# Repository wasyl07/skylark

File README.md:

# skylark
Drone control board based on AM335 BeagleBone Black and Ardupilot

## Repository layout

- `BeagleBone-cape/` - KiCad project of the Skylark cape
- `br2-skylark/` - Buildroot external tree: A/B (RAUC) Linux image with systemd, see [docs/buildroot.md](docs/buildroot.md)
- `buildroot-2025.02.15/` - Buildroot itself (plus the legacy single-slot config, [docs/buildroot-legacy.md](docs/buildroot-legacy.md))
- `scripts/` - image checks (`verify-image.sh`, `check-defconfig.sh`)
- `ardupilot/` - ArduPilot (submodule)
- `docker/` - PRU toolchain container and PRU firmware
- `docs/` - documentation
  - [buildroot.md](docs/buildroot.md) - building, A/B updates, services, flashing, serial console, CAN, RTC/NTP
  - [FUNCTIONS.md](docs/FUNCTIONS.md) - requirements
  - [bringup-2026-10-05.md](docs/bringup-2026-10-05.md) - first bring-up: test results, cape rev 1 issues, board state
  - [prus.md](docs/prus.md) - PRU usage: PRU1 servo/ESC PWM firmware design and ArduPilot interface

## Quick start

```sh
make setup && make                 # -> output/images/sdcard.img, update.raucb
sh scripts/verify-image.sh
```

## Quick reference

- Serial console: UART4, P9.11 (RX) / P9.13 (TX), 115200 8N1, 3.3 V
- Network: DHCP, `skylark.local` (mDNS), SSH as root
- Updates: `rauc install update.raucb` (A/B slots, automatic fallback after 3 failed boots)
- CAN: `can0` (DCAN1, P9.24/P9.26), 1 Mbit/s, up at boot
- RTC: DS1307 on I2C2 (`/dev/rtc1`), synced from NTP when online (cape rev 1: RTC does not keep time, see bring-up record)

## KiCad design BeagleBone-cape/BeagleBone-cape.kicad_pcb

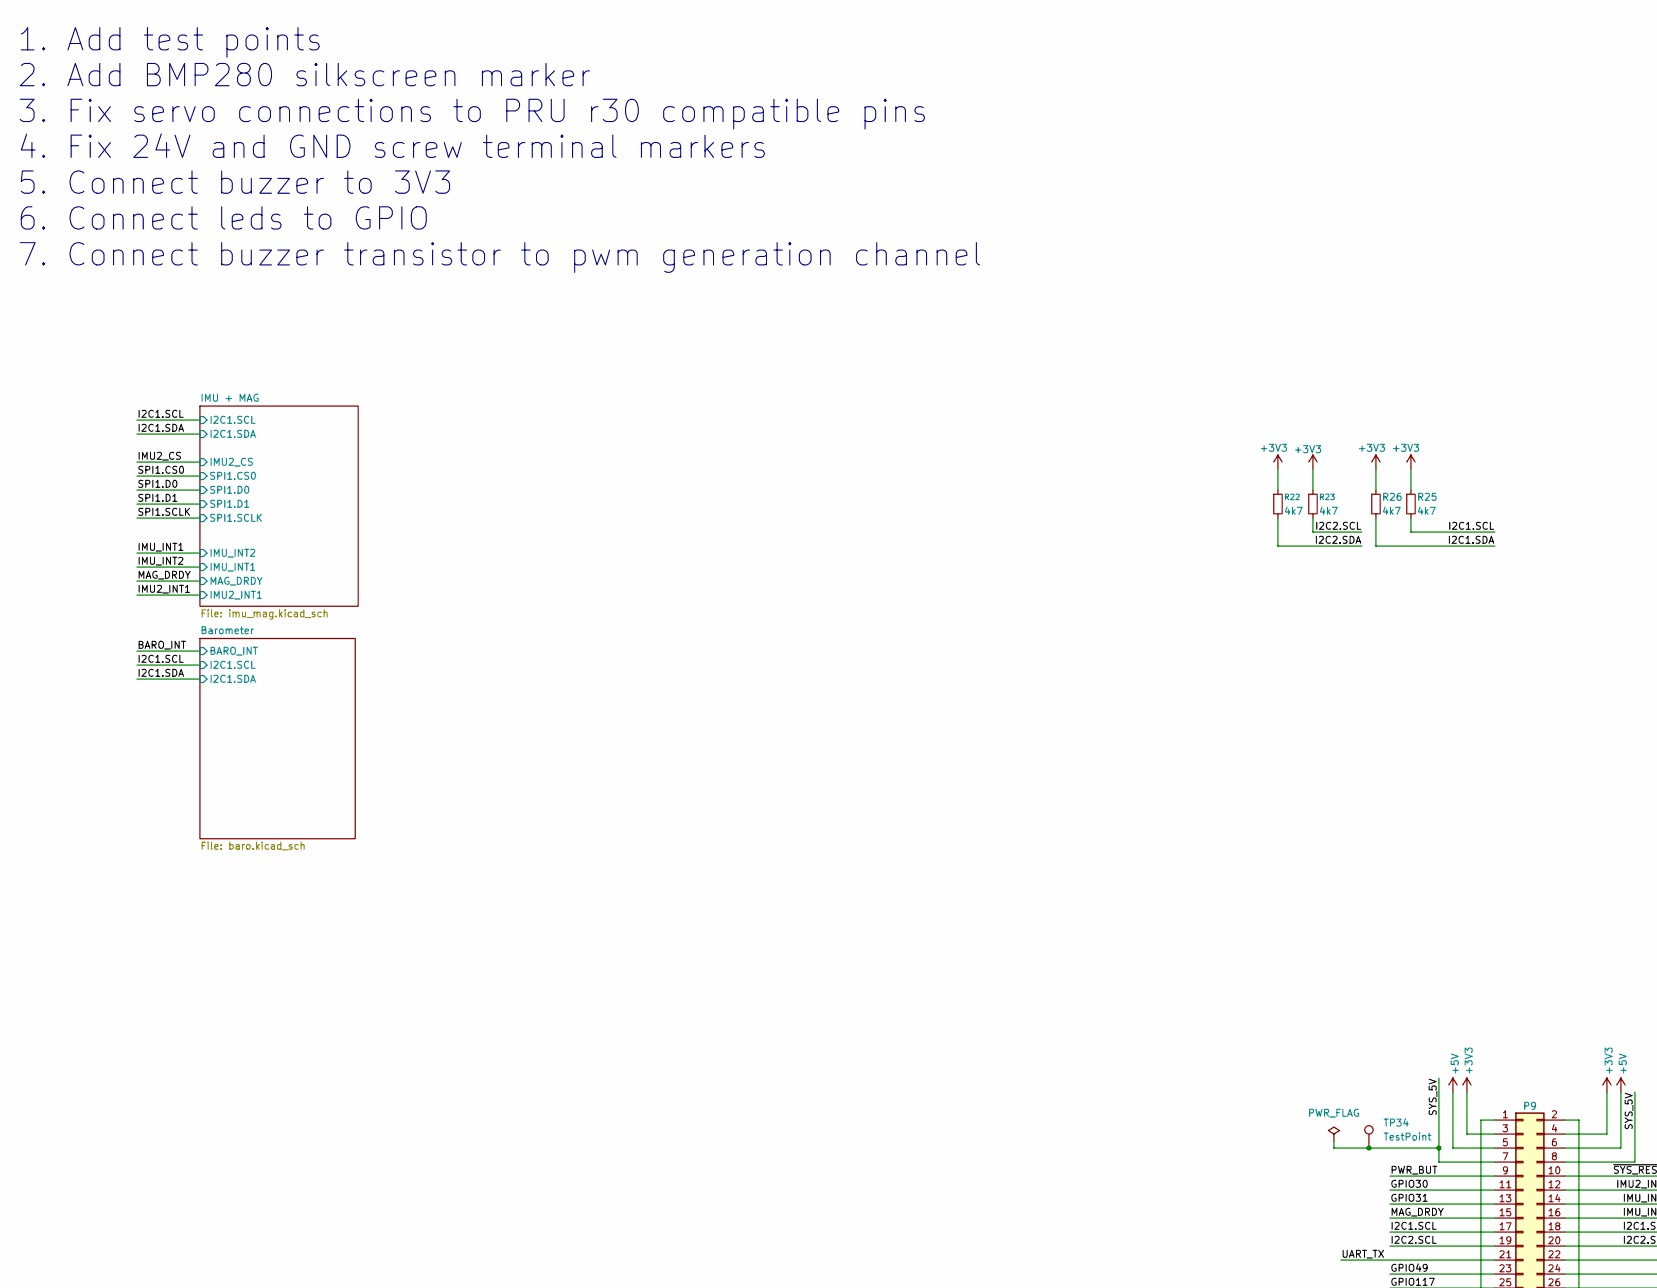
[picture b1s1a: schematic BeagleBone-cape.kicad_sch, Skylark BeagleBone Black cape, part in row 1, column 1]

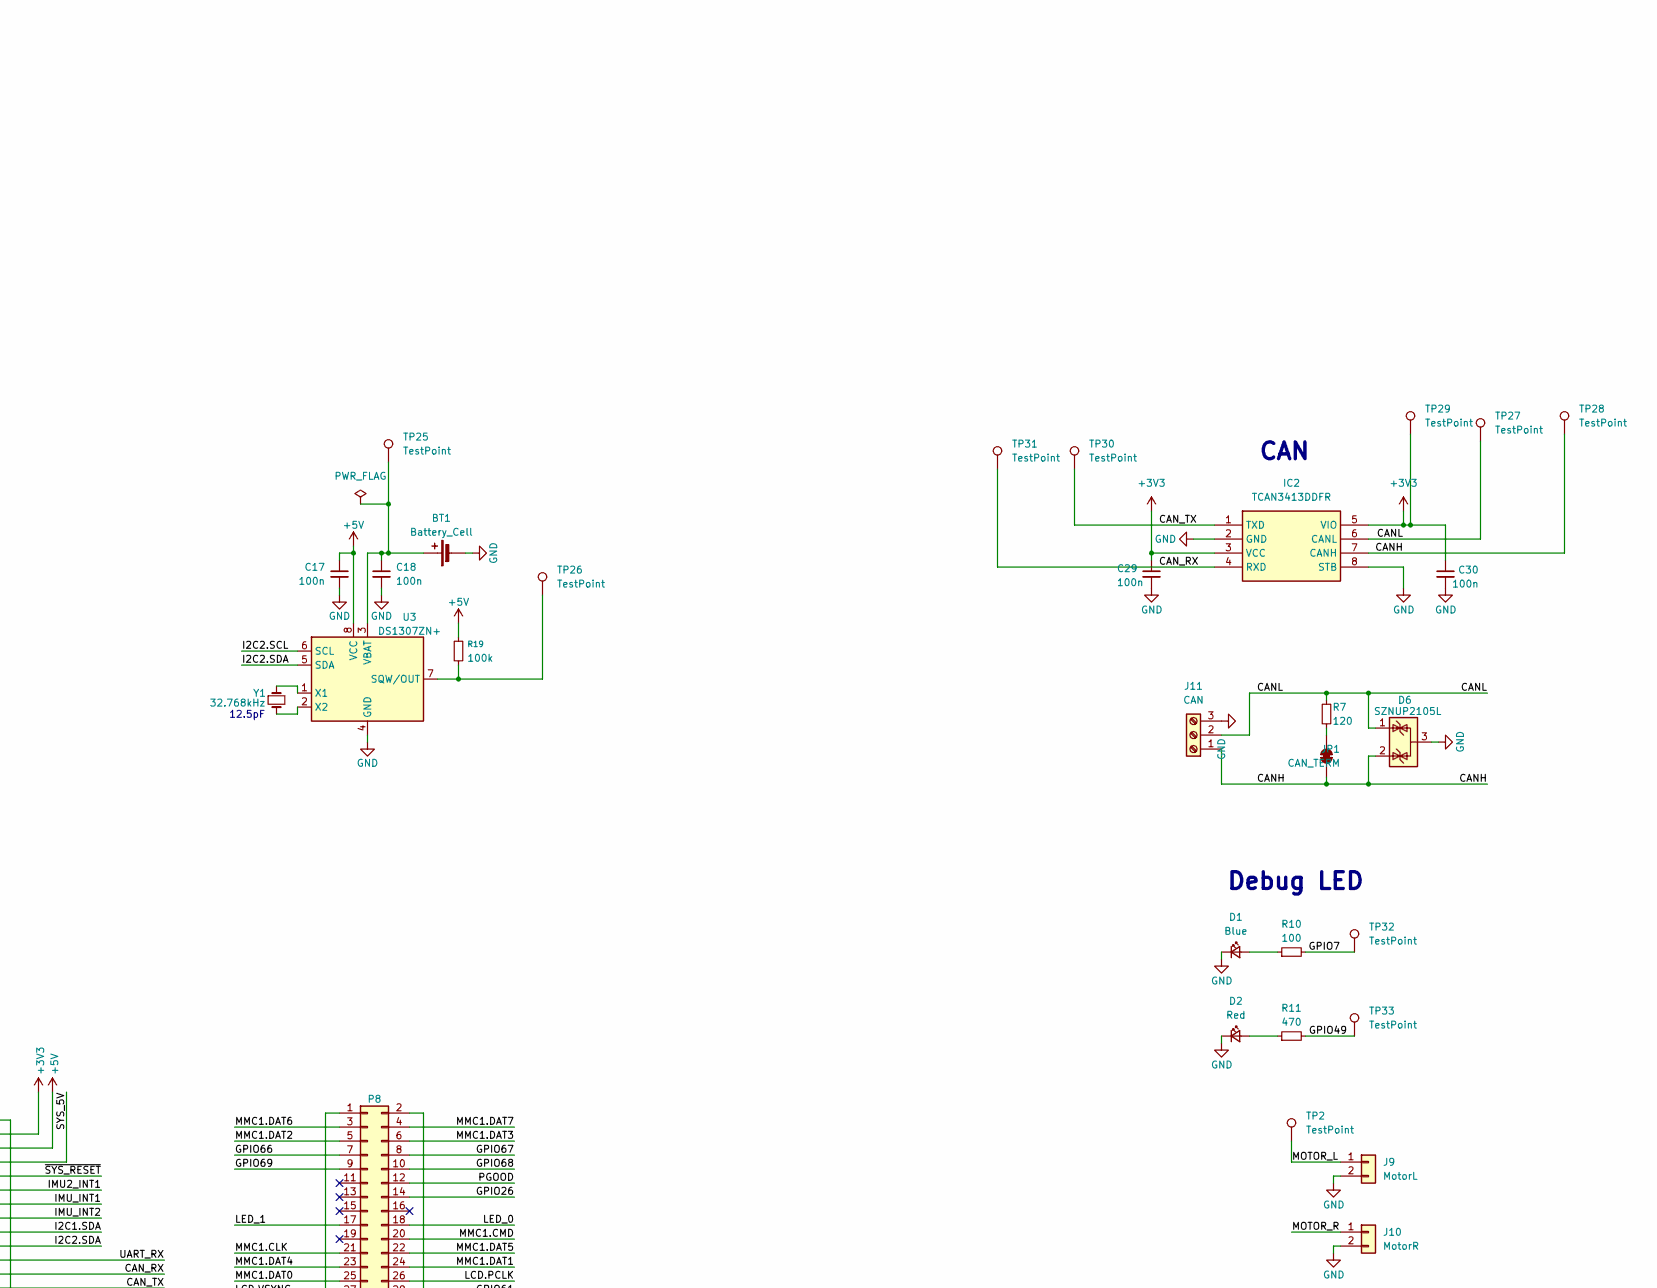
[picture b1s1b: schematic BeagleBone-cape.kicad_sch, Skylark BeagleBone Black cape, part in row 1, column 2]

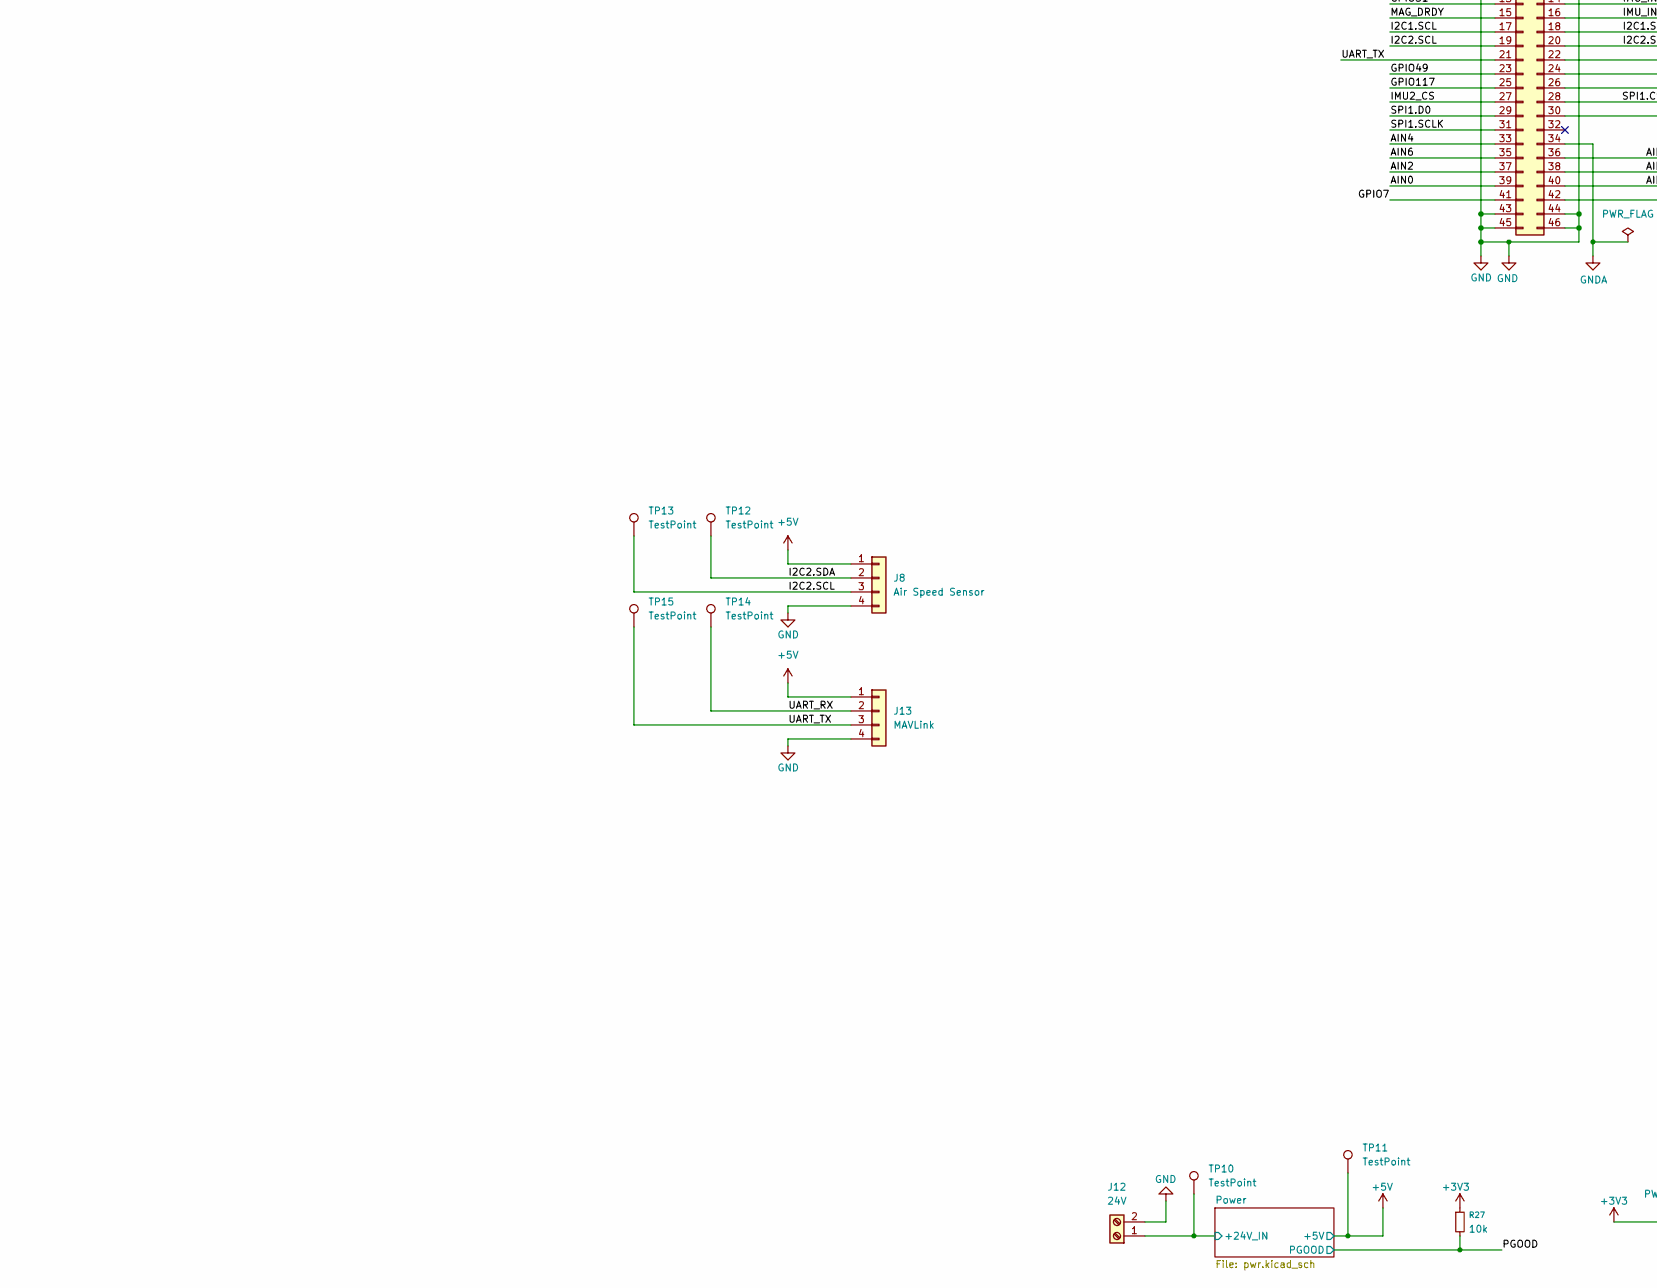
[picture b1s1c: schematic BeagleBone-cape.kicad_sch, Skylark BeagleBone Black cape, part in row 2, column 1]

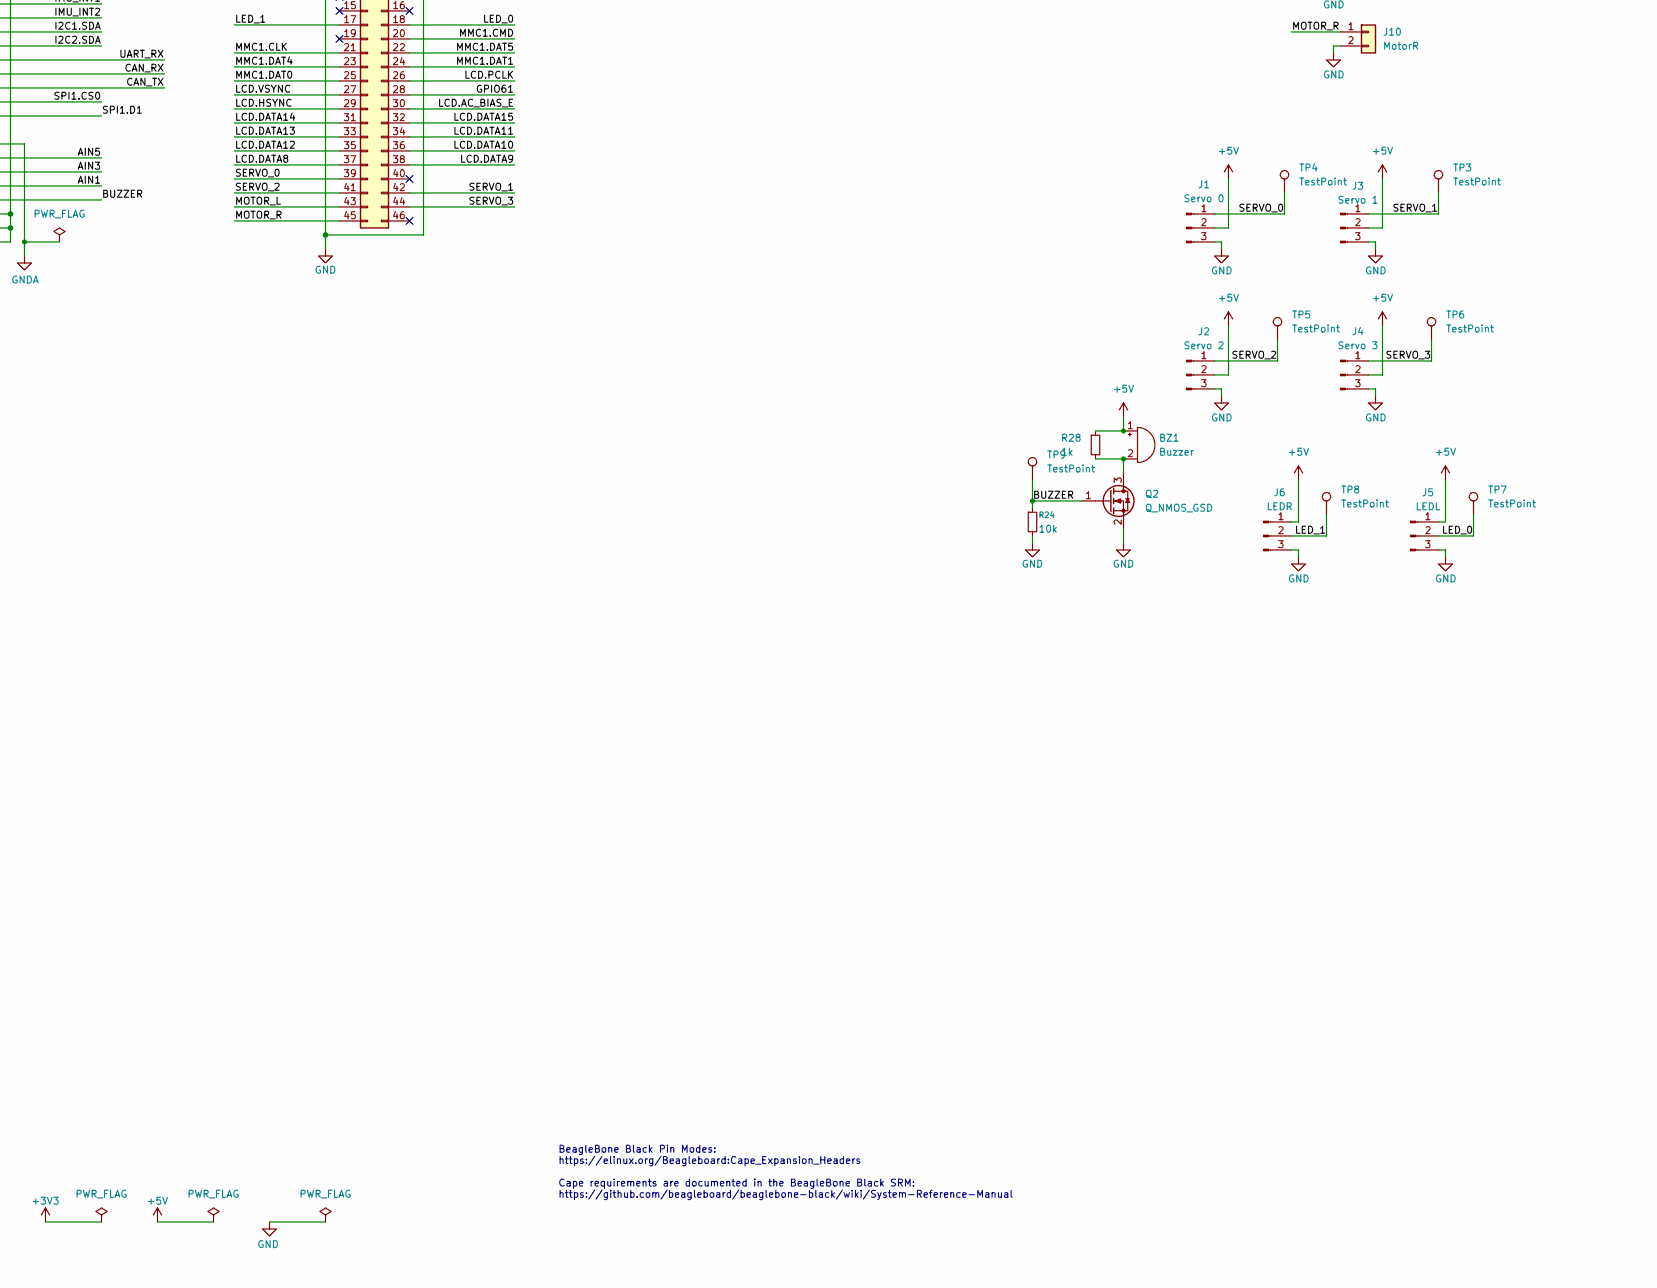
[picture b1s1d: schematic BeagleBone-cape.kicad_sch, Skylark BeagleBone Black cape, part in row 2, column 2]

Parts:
BT1: Battery_Cell; BatteryHolder_MYOUNG_BS-07-A1BJ001_CR2032; Manufacturer_Part_Number BS-07-A1BJ001; LCSC C2979167
BZ1: Buzzer; Buzzer_TDK_PS1240P02BT_D12.2mm_H6.5mm; Manufacturer_Part_Number PS1240P02BT; LCSC C76871
C17, C18, C29, C30: 100n; C_0603_1608Metric_Pad1.08x0.95mm_HandSolder; Manufacturer_Part_Number CC0603KRX7R9BB104; LCSC C14663
D1: Blue; D_0603_1608Metric
D2: Red; D_0603_1608Metric
D6: SZNUP2105L; SOT-23; Manufacturer_Part_Number SZNUP2105LT1G; LCSC C233494
IC2: TCAN3413DDFR; SOT65P280X110-8N; Manufacturer_Part_Number TCAN3413DDFR; Mouser Part Number 595-TCAN3413DDFR
J1: Servo 0; JST_EH_B3B-EH-A_1x03_P2.50mm_Vertical
J2: Servo 2; JST_EH_B3B-EH-A_1x03_P2.50mm_Vertical
J3: Servo 1; JST_EH_B3B-EH-A_1x03_P2.50mm_Vertical
J4: Servo 3; JST_EH_B3B-EH-A_1x03_P2.50mm_Vertical
J5: LEDL; JST_EH_B3B-EH-A_1x03_P2.50mm_Vertical
J6: LEDR; JST_EH_B3B-EH-A_1x03_P2.50mm_Vertical
J8: Air Speed Sensor; JST_EH_B4B-EH-A_1x04_P2.50mm_Vertical
J9: MotorL; JST_EH_B2B-EH-A_1x02_P2.50mm_Vertical
J10: MotorR; JST_EH_B2B-EH-A_1x02_P2.50mm_Vertical
J11: CAN; TerminalBlock_Xinya_XY308-2.54-3P_1x03_P2.54mm_Horizontal
J12: 24V; TerminalBlock_Xinya_XY308-2.54-2P_1x02_P2.54mm_Horizontal
J13: MAVLink; JST_EH_B4B-EH-A_1x04_P2.50mm_Vertical
JP1: CAN_TERM; SolderJumper-2_P1.3mm_Bridged_RoundedPad1.0x1.5mm
P8, P9: BeagleBone_Black_Header; PinHeader_2x23_P2.54mm_Vertical
Q2: Q_NMOS_GSD; SOT-23; Manufacturer_Part_Number BSS138LT1G; LCSC C82045
R7: 120; R_0603_1608Metric_Pad0.98x0.95mm_HandSolder; Manufacturer_Part_Number 0603WAF1200T5E; LCSC C22787
R10: 100; R_0603_1608Metric_Pad0.98x0.95mm_HandSolder; Manufacturer_Part_Number RC0603FR-07100RL; LCSC C105588
R11: 470; R_0603_1608Metric_Pad0.98x0.95mm_HandSolder; Manufacturer_Part_Number 0603WAF4700T5E; LCSC C23179
R19: 100k; R_0603_1608Metric_Pad0.98x0.95mm_HandSolder; Manufacturer_Part_Number RC0603FR-07100KL; LCSC C14675
R22, R23: 4k7; R_0603_1608Metric_Pad0.98x0.95mm_HandSolder; Manufacturer_Part_Number RC0603FR-074K7L; LCSC C99782
R24, R27: 10k; R_0603_1608Metric_Pad0.98x0.95mm_HandSolder; Manufacturer_Part_Number RC0603FR-0710KL; LCSC C98220
R25, R26: 4k7; R_0603_1608Metric_Pad0.98x0.95mm_HandSolder
R28: 1k; R_0603_1608Metric_Pad0.98x0.95mm_HandSolder; Manufacturer_Part_Number 0603WAF1001T5E; LCSC C21190
TP2, TP3, TP4, TP5, TP6, TP7, TP8, TP9, TP10, TP11, TP12, TP13, TP14, TP15, TP25, TP26, TP27, TP28, TP29, TP30, TP31, TP32, TP33, TP34: TestPoint; TestPoint_Pad_D1.0mm
U3: DS1307ZN+; SOIC-8_3.9x4.9mm_P1.27mm; Manufacturer_Part_Number DS1307ZN+T&R; LCSC C26858
Y1: 32.768kHz; Crystal_SMD_3215-2Pin_3.2x1.5mm; Manufacturer_Part_Number Q13FC13500004; LCSC C32346

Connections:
+3V3: C29.1, C30.1, IC2.3 (VCC), IC2.5 (VIO), P9.3, P9.4, R22.1, R23.1, R25.1, R26.1, R27.1, TP29.1; also elsewhere on the board
+5V: BZ1.1 (+), C17.1, J1.2, J2.2, J3.2, J4.2, J5.1, J6.1, J8.1, J13.1, P9.5, P9.6, R19.1, R28.1, TP11.1, U3.8 (VCC); also elsewhere on the board
/AIN0: P9.39
/AIN1: P9.40
/AIN2: P9.37
/AIN3: P9.38
/AIN4: P9.33
/AIN5: P9.36
/AIN6: P9.35
/BUZZER: P9.42, Q2.1 (G), R24.1, TP9.1
/CANH: D6.2 (K), IC2.7 (CANH), J11.1, JP1.1 (A), TP28.1
/CANL: D6.1 (K), IC2.6 (CANL), J11.2, R7.1, TP27.1
/CAN_RX: IC2.4 (RXD), P9.24, TP31.1
/CAN_TX: IC2.1 (TXD), P9.26, TP30.1
/GPIO7: P9.41, R10.2, TP32.1
/GPIO26: P8.14
/GPIO30: P9.11
/GPIO31: P9.13
/GPIO49: P9.23, R11.2, TP33.1
/GPIO61: P8.28
/GPIO66: P8.7
/GPIO67: P8.8
/GPIO68: P8.10
/GPIO69: P8.9
/GPIO117: P9.25
/I2C1.SCL: P9.17, R25.2; also elsewhere on the board
/I2C1.SDA: P9.18, R26.2; also elsewhere on the board
/I2C2.SCL: J8.3, P9.19, R23.2, TP13.1, U3.6 (SCL)
/I2C2.SDA: J8.2, P9.20, R22.2, TP12.1, U3.5 (SDA)
/IMU2_CS: P9.27; also elsewhere on the board
/IMU2_INT1: P9.12; also elsewhere on the board
/IMU_INT1: P9.14; also elsewhere on the board
/IMU_INT2: P9.16; also elsewhere on the board
/LCD.AC_BIAS_E: P8.30
/LCD.DATA8: P8.37
/LCD.DATA9: P8.38
/LCD.DATA10: P8.36
/LCD.DATA11: P8.34
/LCD.DATA12: P8.35
/LCD.DATA13: P8.33
/LCD.DATA14: P8.31
/LCD.DATA15: P8.32
/LCD.HSYNC: P8.29
/LCD.PCLK: P8.26
/LCD.VSYNC: P8.27
/LED_0: J5.2, P8.18, TP7.1
/LED_1: J6.2, P8.17, TP8.1
/MAG_DRDY: P9.15; also elsewhere on the board
/MMC1.CLK: P8.21
/MMC1.CMD: P8.20
/MMC1.DAT0: P8.25
/MMC1.DAT1: P8.24
/MMC1.DAT2: P8.5
/MMC1.DAT3: P8.6
/MMC1.DAT4: P8.23
/MMC1.DAT5: P8.22
/MMC1.DAT6: P8.3
/MMC1.DAT7: P8.4
/MOTOR_L: J9.1, P8.43, TP2.1
/MOTOR_R: J10.1, P8.45
/PGOOD: P8.12, R27.2; also elsewhere on the board
/PWR_BUT: P9.9
/Power/+24V_IN: J12.1, TP10.1; also elsewhere on the board
/SERVO_0: J1.1, P8.39, TP4.1
/SERVO_1: J3.1, P8.42, TP3.1
/SERVO_2: J2.1, P8.41, TP5.1
/SERVO_3: J4.1, P8.44, TP6.1
/SPI1.CS0: P9.28; also elsewhere on the board
/SPI1.D0: P9.29; also elsewhere on the board
/SPI1.D1: P9.30; also elsewhere on the board
/SPI1.SCLK: P9.31; also elsewhere on the board
/SYS_5V: P9.7, P9.8, TP34.1
/UART_RX: J13.2, P9.22, TP14.1
/UART_TX: J13.3, P9.21, TP15.1
/~SYS_RESET: P9.10
GND: BT1.2 (-), C17.2, C18.2, C29.2, C30.2, D1.1 (K), D2.1 (K), D6.3 (A), IC2.2 (GND), IC2.8 (STB), J1.3, J2.3, J3.3, J4.3, J5.3, J6.3, J8.4, J9.2, J10.2, J11.3, J12.2, J13.4, P8.1, P8.2, P9.1, P9.2, P9.43, P9.44, P9.45, P9.46, Q2.2 (S), R24.2, U3.4 (GND); also elsewhere on the board
GNDA: P9.34
unnamed: BT1.1 (+), C18.1, TP25.1, U3.3 (VBAT)
unnamed: BZ1.2 (-), Q2.3 (D), R28.2
unnamed: D1.2 (A), R10.1
unnamed: D2.2 (A), R11.1
unnamed: JP1.2 (B), R7.2
unnamed: R19.2, TP26.1, U3.7 (SQW/OUT)
unnamed: U3.1 (X1), Y1.1
unnamed: U3.2 (X2), Y1.2

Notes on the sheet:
CAN
BeagleBone Black Pin Modes: https://elinux.org/Beagleboard:Cape_Expansion_Headers Cape requirements are documented in the BeagleBone Black SRM: https://github.com/beagleboard/beaglebone-black/wiki/System-Reference-Manual
1. Add test points 2. Add BMP280 silkscreen marker 3. Fix servo connections to PRU r30 compatible pins 4. Fix 24V and GND screw terminal markers 5. Connect buzzer to 3V3 6. Connect leds to GPIO 7. Connect buzzer transistor to pwm generation channel
Debug LED
12.5pF

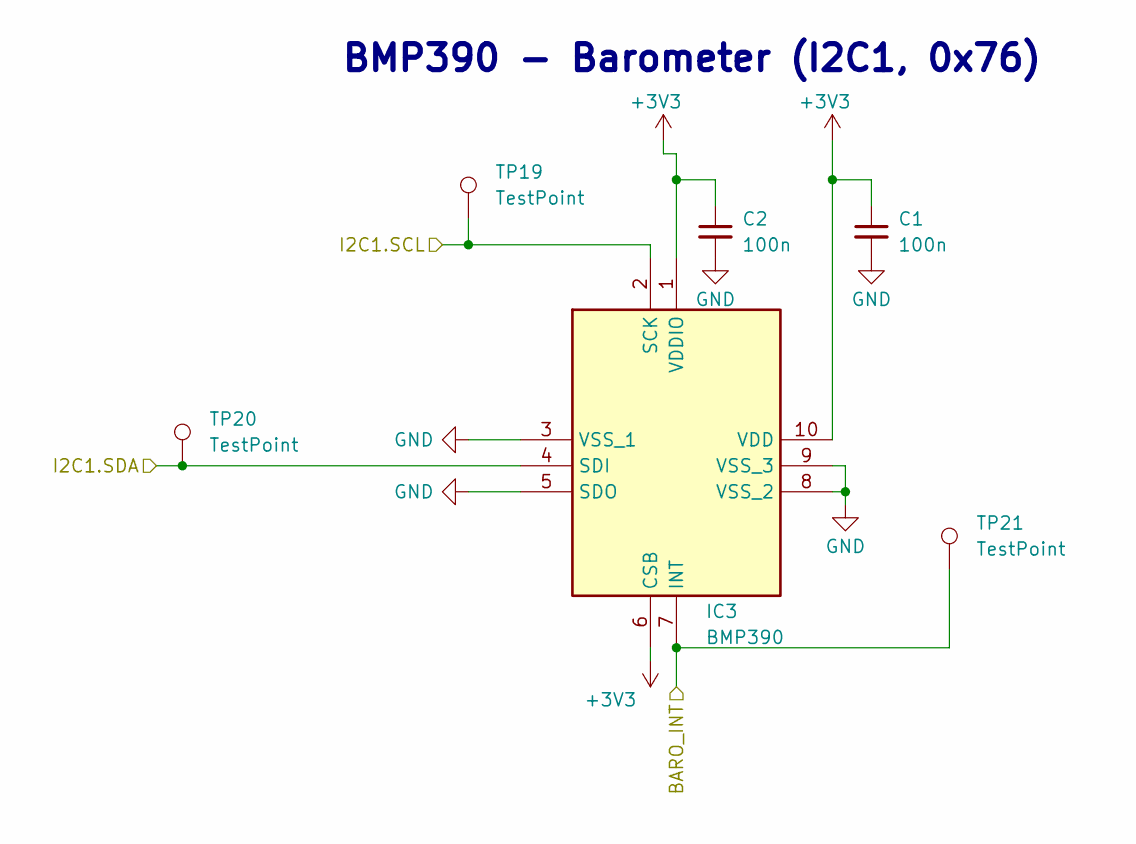
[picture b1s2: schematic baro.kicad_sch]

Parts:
C1, C2: 100n; C_0603_1608Metric_Pad1.08x0.95mm_HandSolder; Manufacturer_Part_Number CC0603KRX7R9BB104; LCSC C14663
IC3: BMP390; Manufacturer_Part_Number BMP390; Mouser Part Number 262-BMP390
TP19, TP20, TP21: TestPoint; TestPoint_Pad_D1.0mm

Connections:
+3V3: C1.1, C2.1, IC3.1 (VDDIO), IC3.6 (CSB), IC3.10 (VDD); also elsewhere on the board
/BARO_INT: IC3.7 (INT), TP21.1
/I2C1.SCL: IC3.2 (SCK), TP19.1; also elsewhere on the board
/I2C1.SDA: IC3.4 (SDI), TP20.1; also elsewhere on the board
GND: C1.2, C2.2, IC3.3 (VSS_1), IC3.5 (SDO), IC3.8 (VSS_2), IC3.9 (VSS_3); also elsewhere on the board

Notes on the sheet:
BMP390 - Barometer (I2C1, 0x76)

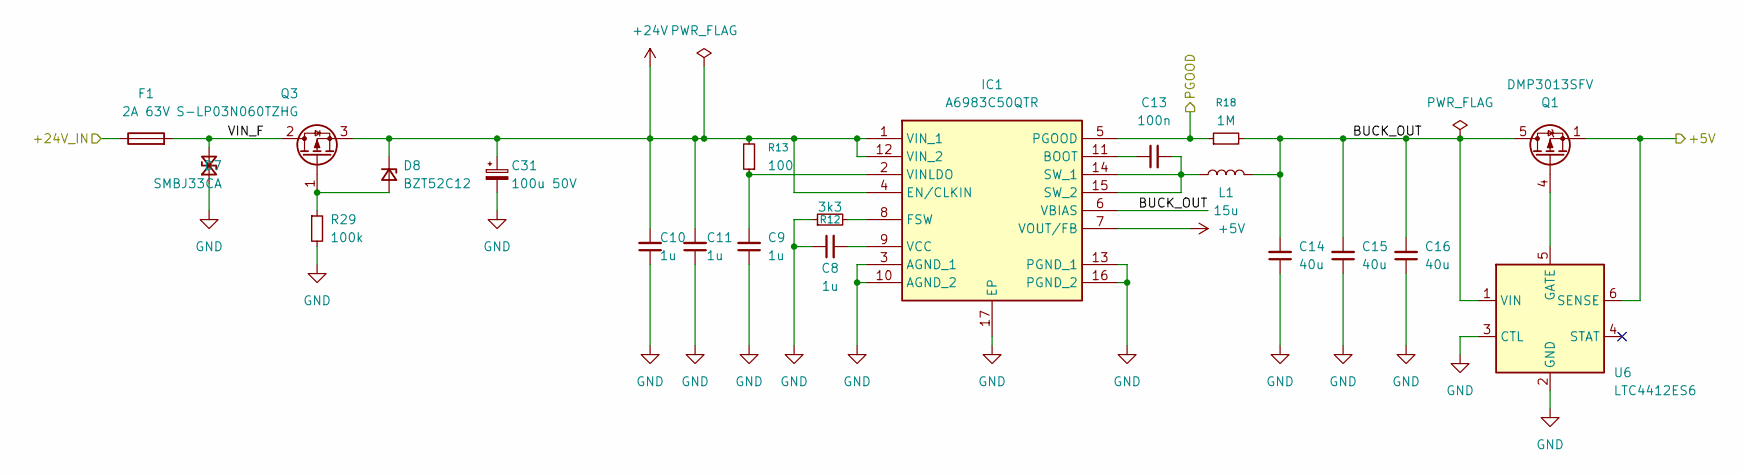
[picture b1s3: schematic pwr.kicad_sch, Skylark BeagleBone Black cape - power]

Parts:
C8, C9, C10, C11: 1u; C_0603_1608Metric_Pad1.08x0.95mm_HandSolder; Manufacturer_Part_Number CL10A105KB8NNNC; LCSC C15849
C13: 100n; C_0603_1608Metric_Pad1.08x0.95mm_HandSolder; Manufacturer_Part_Number CC0603KRX7R9BB104; LCSC C14663
C14, C15, C16: 40u; C_Elec_5x5.4; Manufacturer_Part_Number EFVM016ADA470M0545; LCSC C48935064
C31: 100u 50V; CP_Elec_8x10; Manufacturer_Part_Number EEE-FK1H101P; LCSC C178548
D7: SMBJ33CA; D_SMB; Manufacturer_Part_Number SMBJ33CA; LCSC C78420
D8: BZT52C12; D_SOD-123; Manufacturer_Part_Number BZT52C12-TP; LCSC C668891
F1: 2A 63V; Fuse_1206_3216Metric_Pad1.42x1.75mm_HandSolder; Manufacturer_Part_Number 0466002.NRHF; LCSC C3105
IC1: A6983C50QTR; Manufacturer_Part_Number A6983C50QTR; Mouser Part Number 511-A6983C50QTR
L1: 15u; L_7.3x7.3_H4.5; Manufacturer_Part_Number SDRH.0704CT.NLF150MT00; LCSC C5123035
Q1: DMP3013SFV; Diodes_PowerDI3333-8
Q3: S-LP03N060TZHG; SOT-223-3_TabPin2; Manufacturer_Part_Number S-LP03N060TZHG; LCSC C5200150
R12: 3k3; R_0603_1608Metric_Pad0.98x0.95mm_HandSolder; Manufacturer_Part_Number 0603WAF3301T5E; LCSC C22978
R13: 100; R_0603_1608Metric_Pad0.98x0.95mm_HandSolder; Manufacturer_Part_Number RC0603FR-07100RL; LCSC C105588
R18: 1M; R_0603_1608Metric_Pad0.98x0.95mm_HandSolder; Manufacturer_Part_Number RC0603FR-071ML; LCSC C105578
R29: 100k; R_0603_1608Metric_Pad0.98x0.95mm_HandSolder; Manufacturer_Part_Number RC0603FR-07100KL; LCSC C14675
U6: LTC4412ES6; TSOT-23-6

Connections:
+5V: IC1.7 (VOUT/FB), Q1.1 (S), Q1.2 (S), Q1.3 (S), U6.6 (SENSE); also elsewhere on the board
+24V: C10.2, C11.2, C31.1, D8.1 (K), IC1.1 (VIN_1), IC1.4 (EN/CLKIN), IC1.12 (VIN_2), Q3.3 (S), R13.2
/PGOOD: IC1.5 (PGOOD), R18.1; also elsewhere on the board
/Power/+24V_IN: F1.1; also elsewhere on the board
/Power/BUCK_OUT: C14.2, C15.2, C16.2, IC1.6 (VBIAS), L1.2, Q1.5 (D), R18.2, U6.1 (VIN)
/Power/VIN_F: D7.2 (A2), F1.2, Q3.2 (D)
GND: C8.1, C9.1, C10.1, C11.1, C14.1, C15.1, C16.1, C31.2, D7.1 (A1), IC1.3 (AGND_1), IC1.10 (AGND_2), IC1.13 (PGND_1), IC1.16 (PGND_2), IC1.17 (EP), R12.1, R29.2, U6.2 (GND), U6.3 (CTL); also elsewhere on the board
unnamed: D8.2 (A), Q3.1 (G), R29.1
unnamed: C13.1, IC1.11 (BOOT)
unnamed: IC1.8 (FSW), R12.2
unnamed: C13.2, IC1.14 (SW_1), IC1.15 (SW_2), L1.1
unnamed: C8.2, IC1.9 (VCC)
unnamed: C9.2, IC1.2 (VINLDO), R13.1
unnamed: Q1.4 (G), U6.5 (GATE)

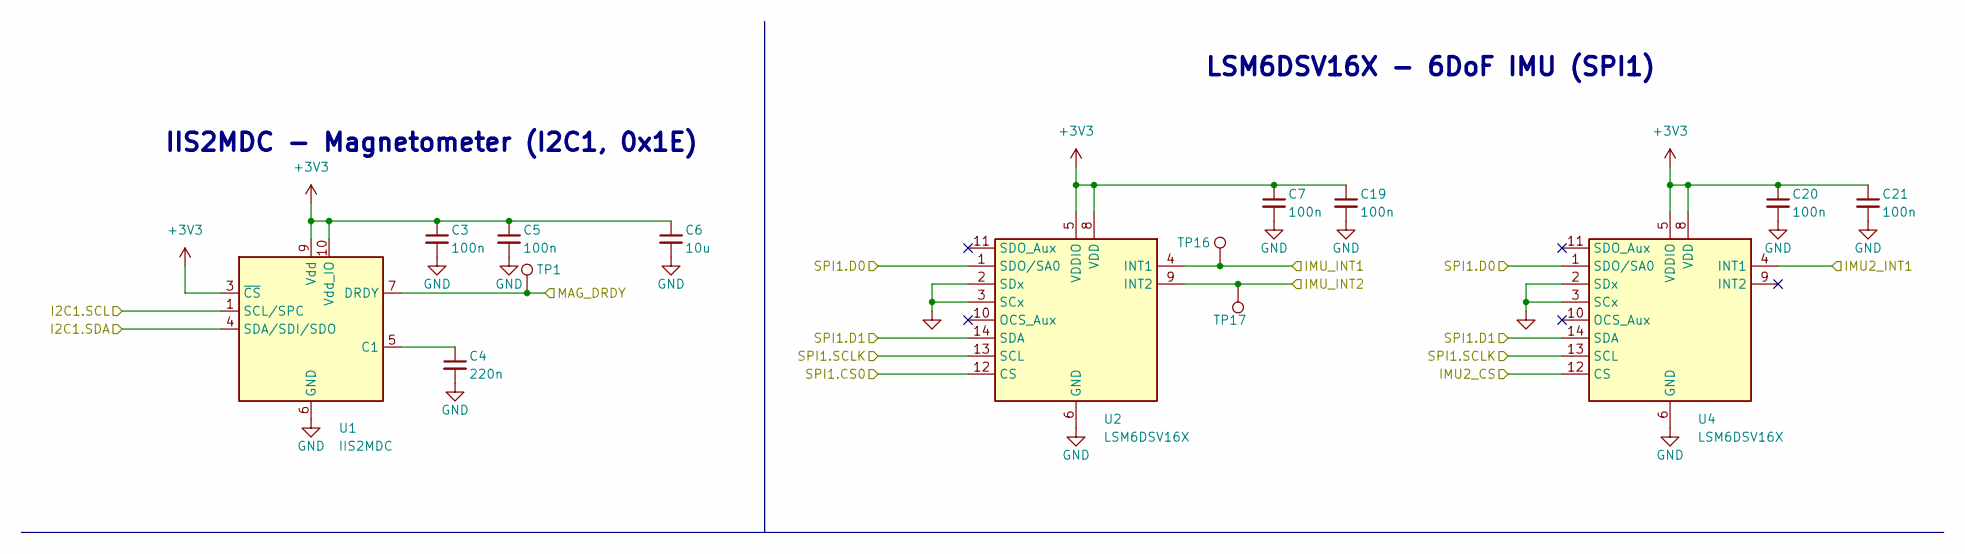
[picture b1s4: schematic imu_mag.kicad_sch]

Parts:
C3, C5, C7, C19, C20, C21: 100n; C_0603_1608Metric_Pad1.08x0.95mm_HandSolder; Manufacturer_Part_Number CC0603KRX7R9BB104; LCSC C14663
C4: 220n; C_0603_1608Metric_Pad1.08x0.95mm_HandSolder; Part number 220n-50V-X7R-10%; LCSC C6119835
C6: 10u; C_0603_1608Metric_Pad1.08x0.95mm_HandSolder; Manufacturer_Part_Number CL10A106KP8NNNC; LCSC C19702
TP1, TP16, TP17: TestPoint; TestPoint_Pad_D1.0mm
U1: IIS2MDC; LGA-12_2x2mm_P0.5mm; Manufacturer_Part_Number IIS2MDCTR
U2, U4: LSM6DSV16X; LGA-14_3x2.5mm_P0.5mm_LayoutBorder3x4y; Manufacturer_Part_Number LSM6DSV16XTR

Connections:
+3V3: C3.1, C5.1, C6.1, C7.1, C19.1, C20.1, C21.1, U1.3 (~CS), U1.9 (Vdd), U1.10 (Vdd_IO), U2.5 (VDDIO), U2.8 (VDD), U4.5 (VDDIO), U4.8 (VDD); also elsewhere on the board
/I2C1.SCL: U1.1 (SCL/SPC); also elsewhere on the board
/I2C1.SDA: U1.4 (SDA/SDI/SDO); also elsewhere on the board
/IMU2_CS: U4.12 (CS); also elsewhere on the board
/IMU2_INT1: U4.4 (INT1); also elsewhere on the board
/IMU_INT1: TP17.1, U2.9 (INT2); also elsewhere on the board
/IMU_INT2: TP16.1, U2.4 (INT1); also elsewhere on the board
/MAG_DRDY: TP1.1, U1.7 (DRDY); also elsewhere on the board
/SPI1.CS0: U2.12 (CS); also elsewhere on the board
/SPI1.D0: U2.1 (SDO/SA0), U4.1 (SDO/SA0); also elsewhere on the board
/SPI1.D1: U2.14 (SDA), U4.14 (SDA); also elsewhere on the board
/SPI1.SCLK: U2.13 (SCL), U4.13 (SCL); also elsewhere on the board
GND: C3.2, C4.2, C5.2, C6.2, C7.2, C19.2, C20.2, C21.2, U1.6 (GND), U1.8 (GND), U2.2 (SDx), U2.3 (SCx), U2.6 (GND), U2.7 (GND), U4.2 (SDx), U4.3 (SCx), U4.6 (GND), U4.7 (GND); also elsewhere on the board
unnamed: C4.1, U1.5 (C1)

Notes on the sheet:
LSM6DSV16X - 6DoF IMU (SPI1)
IIS2MDC - Magnetometer (I2C1, 0x1E)

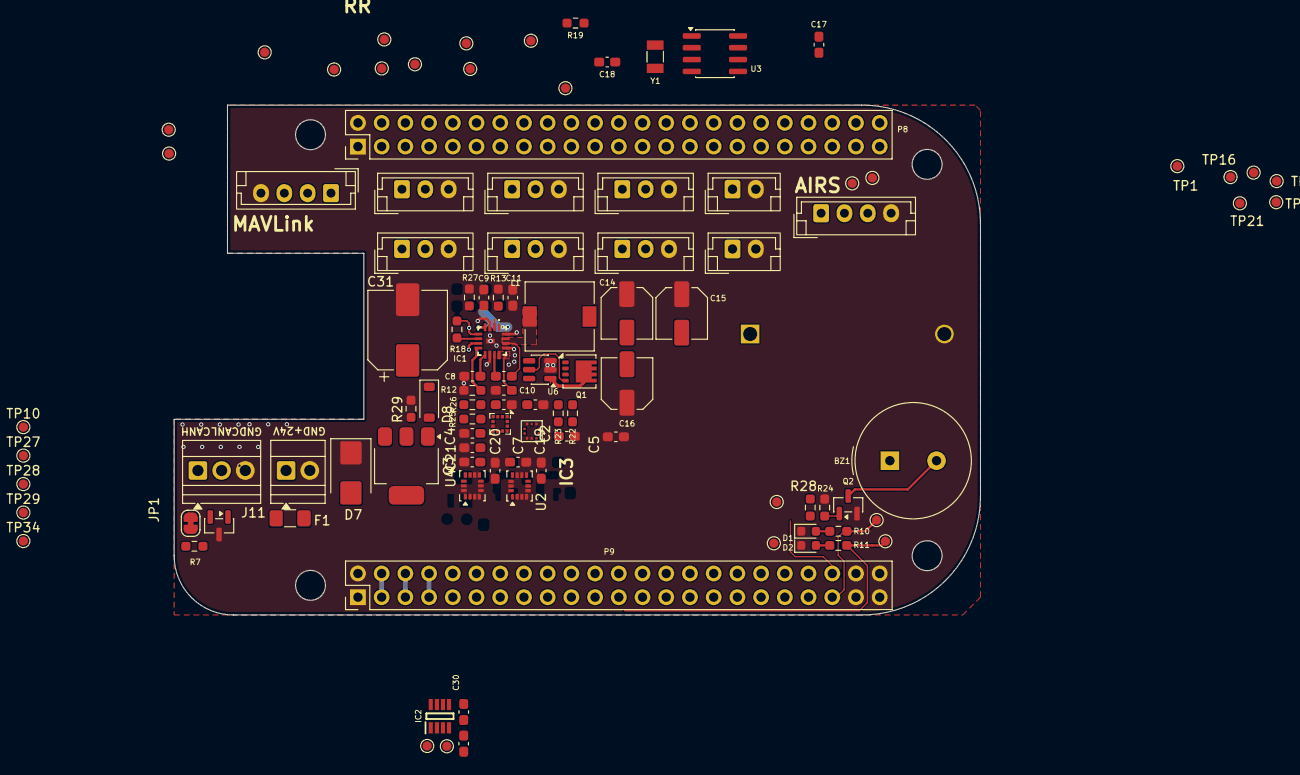
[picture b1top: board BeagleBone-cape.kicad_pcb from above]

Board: 4 copper layers, 86.4 x 54.6 mm, 108 parts (1 on the bottom side), 56 nets.

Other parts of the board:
MH1, MH2, MH3, MH4: MountingHole_3.2mm_M3_DIN965

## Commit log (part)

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2026-06-28 Add cape project
2026-06-28 Add buildroot project
2026-06-28 Add ardupilot
2026-06-28 Add prus docs
